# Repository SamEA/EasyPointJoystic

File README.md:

EasyPointJoystic
================

N40P107 + AS5013  = Easy Point Joystic

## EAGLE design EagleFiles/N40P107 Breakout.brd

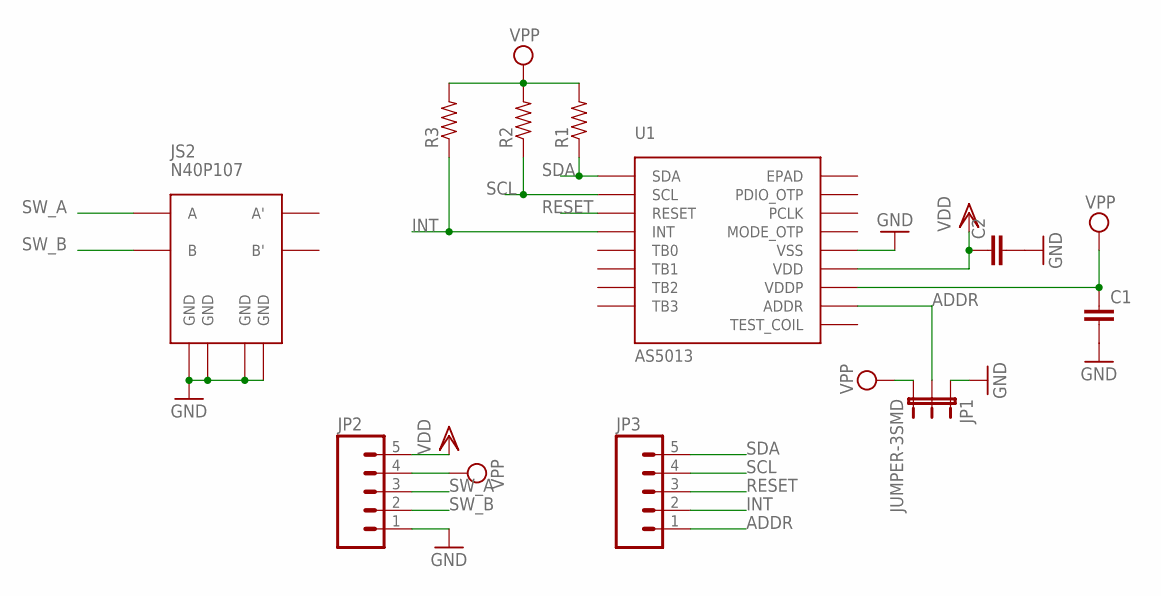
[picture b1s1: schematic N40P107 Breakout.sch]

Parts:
C1, C2: CAP0603-CAP; 0603-CAP
JP1: JUMPER-3SMD; SJ_3
JP2, JP3: M05PTH; 1X05
JS2: N40P107
R1, R2, R3: RESISTOR0402-RES; 0402-RES
U1: AS5013

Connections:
ADDR: JP1.2, JP3.1, U1.10 (ADDR)
GND: C1.2, C2.2, JP1.1, JP2.1, JS2.1 (GND), JS2.4 (GND), JS2.5 (GND), JS2.8 (GND), U1.13 (VSS)
INT: JP3.2, R3.1, U1.4 (INT)
RESET: JP3.3, U1.3 (RESET)
SCL: JP3.4, R2.1, U1.2 (SCL)
SDA: JP3.5, R1.1, U1.1 (SDA)
SW_A: JP2.3, JS2.2 (A)
SW_B: JP2.2, JS2.3 (B)
VDD: C2.1, JP2.5, U1.12 (VDD)
VPP: C1.1, JP1.3, JP2.4, R1.2, R2.2, R3.2, U1.11 (VDDP)

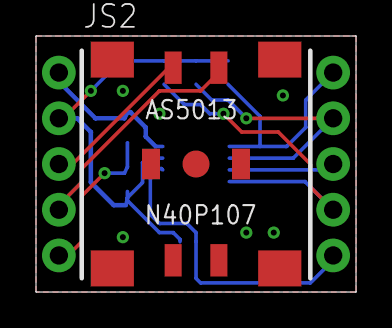
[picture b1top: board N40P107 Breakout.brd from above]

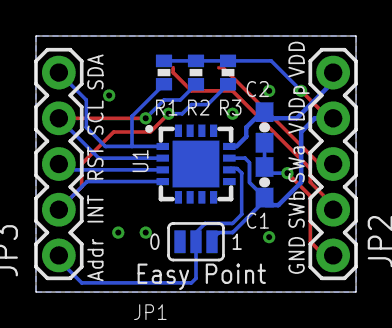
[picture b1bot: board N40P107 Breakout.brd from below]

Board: 2 copper layers, 17.8 x 14.2 mm, 10 parts (9 on the bottom side), 10 nets.

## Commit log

2013-08-06 Initial Comm
2013-09-28 Added picture
2013-10-03 Added Part Library

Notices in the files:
parts and their libraries:
SparkFun-Passives: Licensing: CC v3.0 Share-Alike You are welcome to use this library for commercial purposes.
